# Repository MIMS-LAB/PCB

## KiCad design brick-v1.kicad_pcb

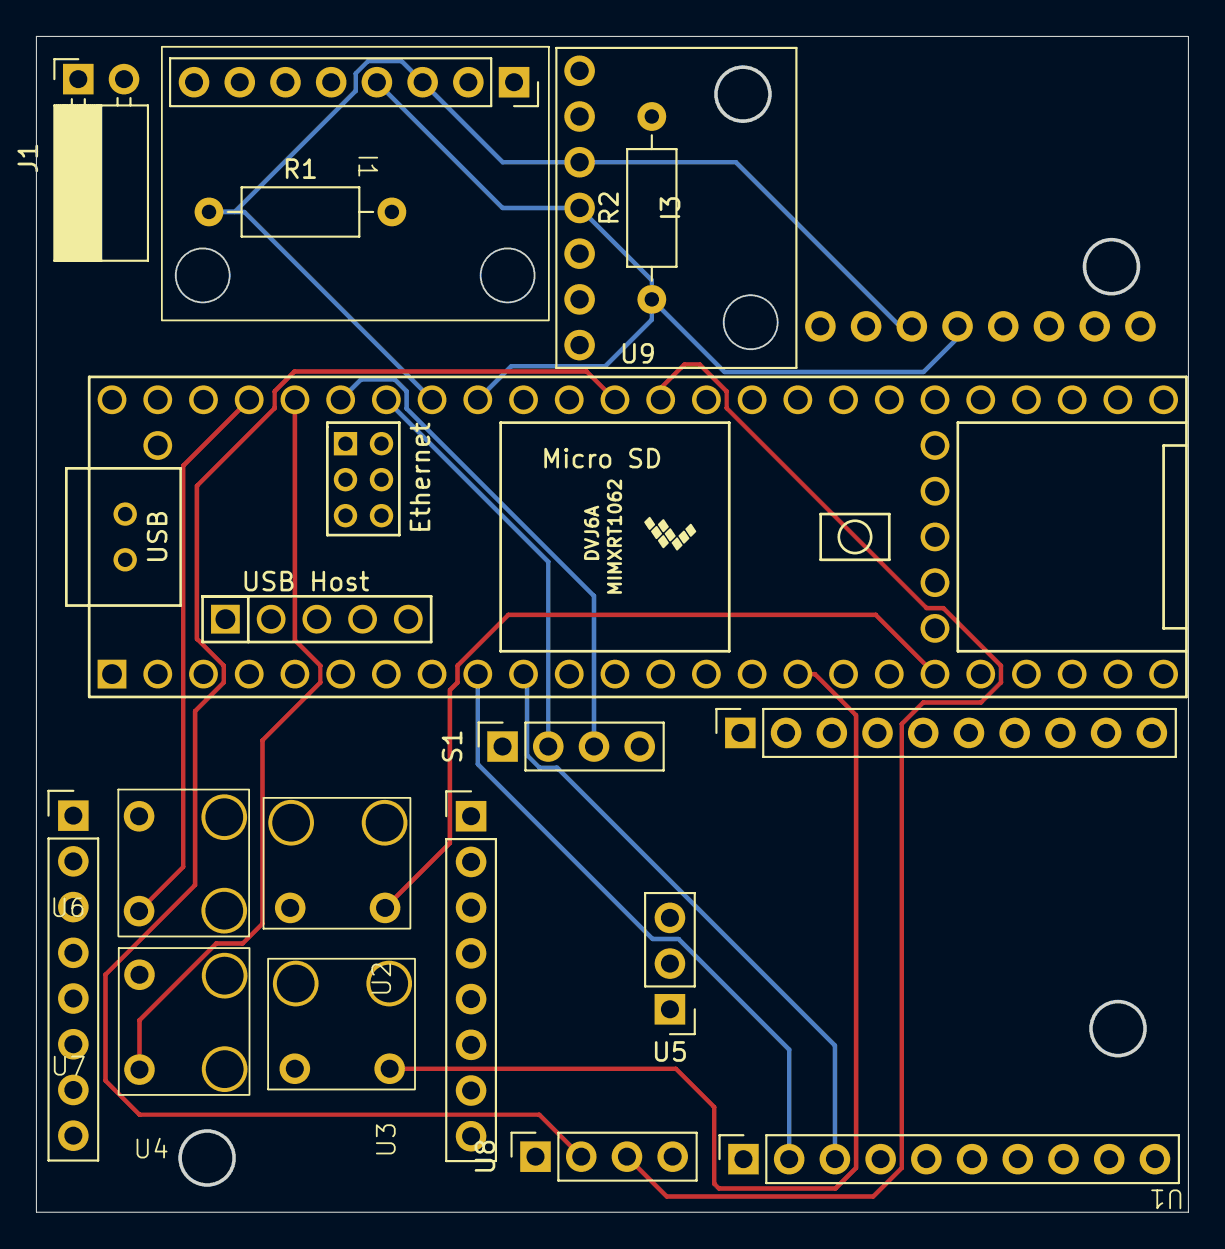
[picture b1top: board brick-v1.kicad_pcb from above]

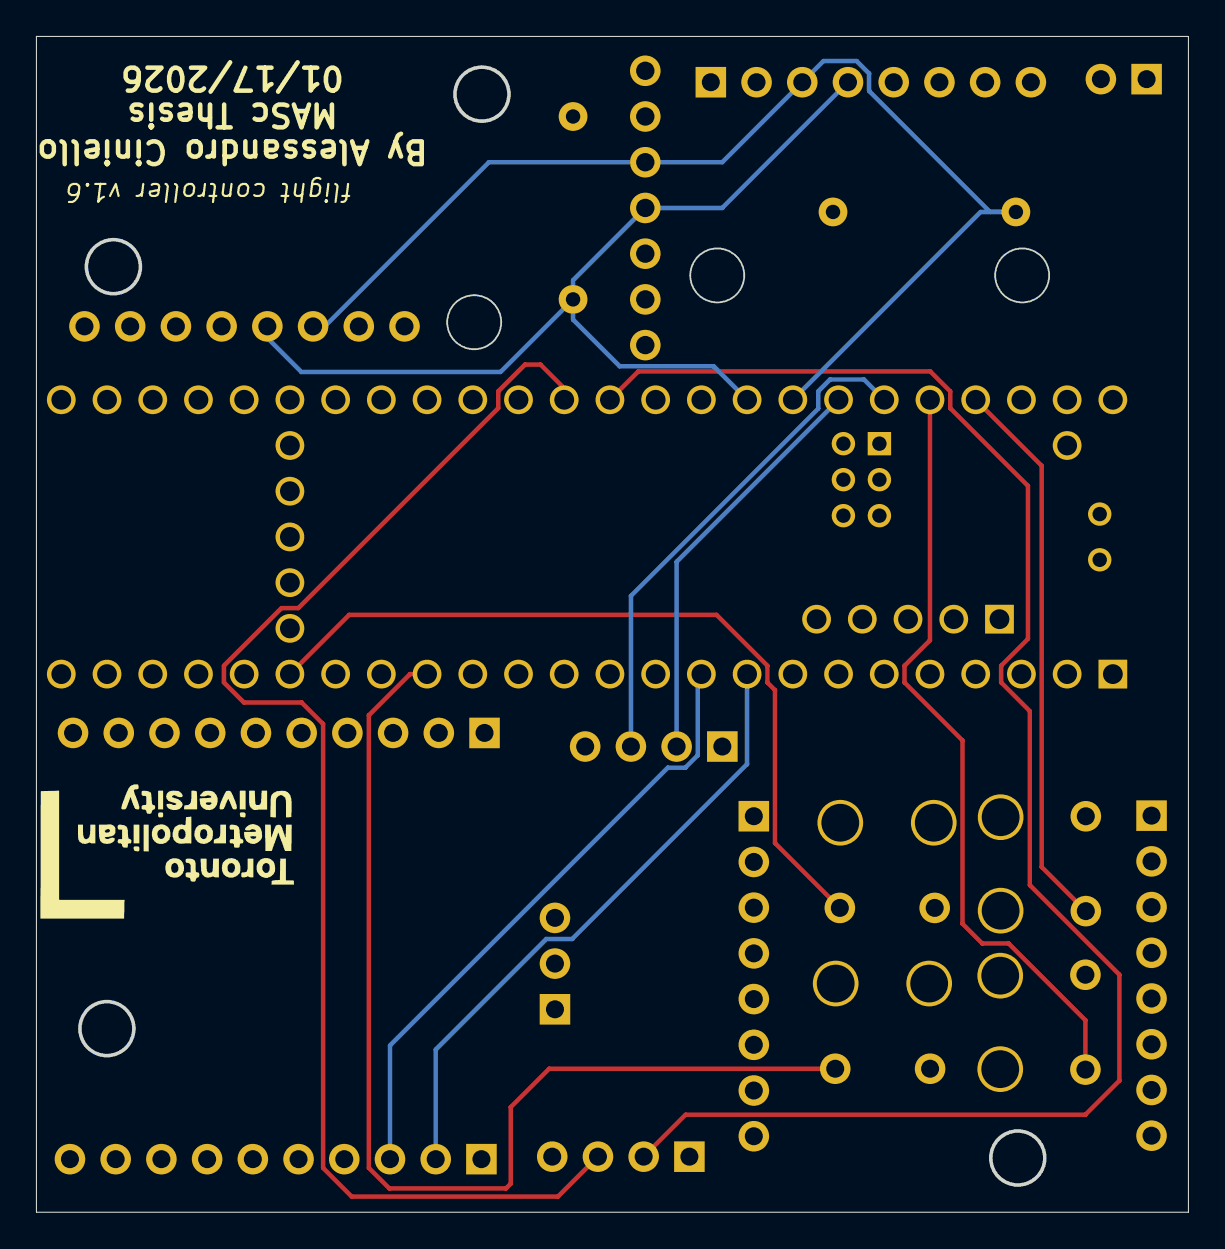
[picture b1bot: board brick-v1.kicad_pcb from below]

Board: 4 copper layers, 64.0 x 65.3 mm, 17 parts (2 on the bottom side), 16 nets.

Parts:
I1: MPU6050
I2: INA260
I3: MS5611; 1x07
J1: battery_header; PinSocket_1x02_P2.54mm_Horizontal
Logo1: picturae
R1, R2: R-Device; R_Axial_DIN0207_L6.3mm_D2.5mm_P10.16mm_Horizontal
S1: BN220-GPS; PinSocket_1x04_P2.54mm_Vertical
U1: XBEE S2C PRO; xbee_s2c
U2, U3, U6, U7: ESC; BLHeLi_esc
U4: esp32; esp32_cam
U5: L7805; PinHeader_1x03_P2.54mm_Vertical
U8: ULTRASONIC SENSOR; PinSocket_1x04_P2.54mm_Vertical
U9: Teensy4.1; Teensy41

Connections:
A0: U8.3 (ECHO), U9.14 (14_A0_TX3_SPDIF_OUT)
A1: U8.2 (TRIG), U9.15 (15_A1_RX3_SPDIF_IN)
A8: U7.4 (PWM), U9.22 (22_A8_CTX1)
A9: U6.4 (PWM), U9.23 (23_A9_CRX1_MCLK1)
A10: U3.4 (PWM), U9.24 (24_A10_TX6_SCL2)
A13: U2.4 (PWM), U9.27 (27_A13_SCK1)
GND: I1.2 (GND), I2.4 (GND), I3.2 (GND), J1.1, S1.4 (GND), U1.10 (GND), U2.2 (GND), U2.3 (T_GND), U3.2 (GND), U3.3 (T_GND), U4.2 (GND), U5.2 (GND), U6.2 (GND), U6.3 (T_GND), U7.2 (GND), U7.3 (T_GND), U8.4 (GND), U9.GND0 (GND), U9.GND2 (GND)
RX2: U1.2 (DOUT/DIO13), U9.7 (7_RX2_OUT1A)
RX5: S1.3 (TX), U9.21 (21_A7_RX5_BCLK1)
SCL: I1.3 (SCL), I2.5 (SCL), I3.3 (SCL), R1.1, U9.19 (19_A5_SCL)
SDA: I1.4 (SDA), I2.6 (SDA), I3.4 (SDA), R2.1, U9.18 (18_A4_SDA)
TX2: U1.3 (DIN/~CONFIG~{/DIO14), U9.8 (8_TX2_IN1)
TX5: S1.2 (RX), U9.20 (20_A6_TX5_LRCLK1)
T_VCC: I1.1 (VCC), I2.3 (VCC), I3.1 (VCC), R1.2, R2.2, U1.1 (VCC), U9.3.3V_1 (3V3)
VCC: S1.1 (VCC), U4.1 (VCC), U5.3 (OUT), U8.1 (VCC), U9.VIN
Vs: I2.1 (VIN+), J1.2, U2.1 (VCC), U3.1 (VCC), U5.1 (IN), U6.1 (VCC), U7.1 (VCC)

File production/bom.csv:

Designator,Footprint,Quantity,Value,LCSC Part #
I1,MPU6050,1,MPU6050,
I2,INA260,1,INA260,
I3,1x07,1,MS5611,
J1,PinSocket_1x02_P2.54mm_Horizontal,1,battery_header,
"LOGO1, LOGO2",picturae,2,~,
"R1, R2",R_Axial_DIN0207_L6.3mm_D2.5mm_P10.16mm_Horizontal,2,R-Device,
S1,PinSocket_1x04_P2.54mm_Vertical,1,BN220-GPS,
U1,xbee_s2c,1,XBEE S2C PRO,
"U2, U3, U6, U7",BLHeLi_esc,4,ESC,
U4,esp32_cam,1,esp32,
U5,PinHeader_1x03_P2.54mm_Vertical,1,L7805,
U8,PinSocket_1x04_P2.54mm_Vertical,1,ULTRASONIC SENSOR,
U9,Teensy41,1,Teensy4.1,

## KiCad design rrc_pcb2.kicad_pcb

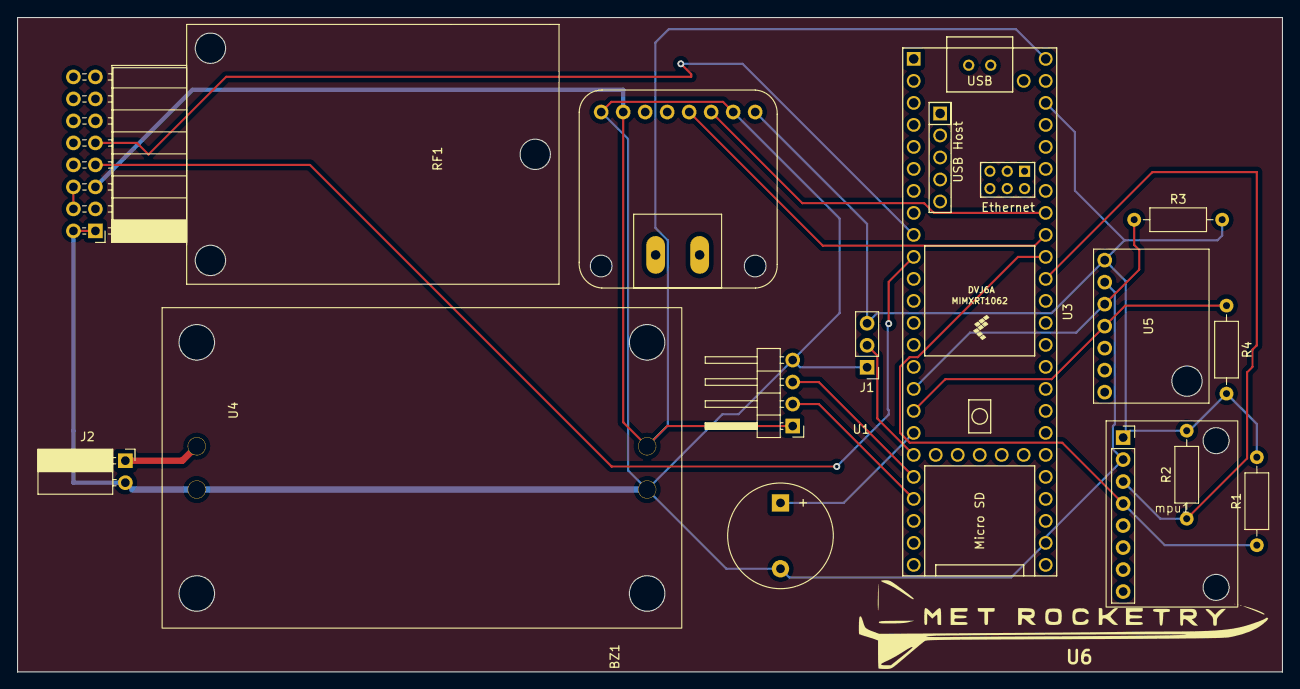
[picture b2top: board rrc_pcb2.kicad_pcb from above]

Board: 2 copper layers, 146.1 x 75.6 mm, 15 parts (0 on the bottom side), 15 nets.

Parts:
BZ1: Buzzer-Device; Buzzer_12x9.5RM7.6
J1: buzzer_toggle_pin; PinHeader_1x03_P2.54mm_Vertical
J2: battery_header; PinSocket_1x02_P2.54mm_Horizontal
R1, R2, R3, R4: R-Device; R_Axial_DIN0207_L6.3mm_D2.5mm_P10.16mm_Horizontal
RF1: RFD900+-RF_Module; RFD900+
U1: BN220-GPS; BN220
U2: INA260
U3: Teensy4.1; Teensy41
U4: voltReg
U5: MS5611; 1x07
U6: logo; RRC_logo
mpu1: MPU6050

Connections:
GND: BZ1.2 (+), J1.1, J2.2, RF1.GND, U1.4 (GND), U2.4 (GND), U2.10 (IN-), U3.34 (GND), U4.2 (GND), U4.4 (GND), U5.2 (GND), mpu1.2 (GND)
unnamed: BZ1.1 (-), U3.26 (26_A12_MOSI1)
unnamed: J1.2, U3.27 (27_A13_SCK1)
unnamed: J2.1, U4.1 (7.2V)
RX7: U1.3 (TX), U3.28 (28_RX7)
SCL: U2.5 (SCL), U3.19 (19_A5_SCL)
SCL1: R2.1, U3.16 (16_A2_RX4_SCL1), mpu1.3 (SCL)
SCL2: R3.1, U3.24 (24_A10_TX6_SCL2), U5.3 (SCL)
SDA: U2.6 (SDA), U3.18 (18_A4_SDA)
SDA1: R1.1, U3.17 (17_A3_TX4_SDA1), mpu1.4 (SDA)
SDA2: R4.1, U3.25 (25_A11_RX6_SDA2), U5.4 (SDA)
TX2: RF1.SIRX, U3.8 (8_TX2_IN1)
TX7: U1.2 (RX), U3.29 (29_TX7)
T_VCC: J1.3, R1.2, R2.2, R3.2, R4.2, U2.3 (VCC), U5.1 (VCC), mpu1.1 (VCC)
VCC: RF1.+5VUSB, U1.1 (VCC), U2.9 (IN+), U3.VIN, U4.3 (5V)

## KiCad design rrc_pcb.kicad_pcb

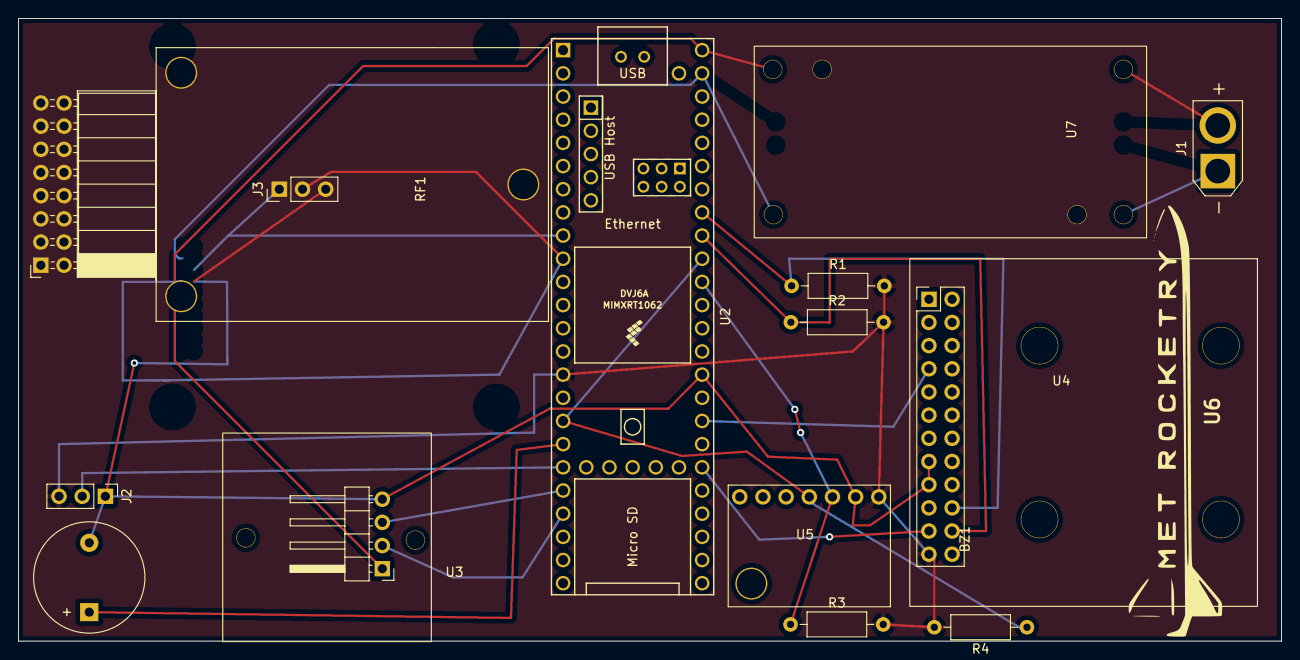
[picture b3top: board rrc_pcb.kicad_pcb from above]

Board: 2 copper layers, 138.4 x 68.2 mm, 15 parts (0 on the bottom side), 18 nets.

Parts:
BZ1: Buzzer-Device; Buzzer_12x9.5RM7.6
J1: Conn_01x02_Male-Connector; AMASS_XT30U-F_1x02_P5.0mm_Vertical
J2: Conn_01x03_Male-Connector; PinHeader_1x03_P2.54mm_Vertical
J3: digital logic connection; PinHeader_1x03_P2.54mm_Vertical
R1, R2, R3, R4: R-Device; R_Axial_DIN0207_L6.3mm_D2.5mm_P10.16mm_Horizontal
RF1: RFD900+-RF_Module; RFD900+
U2: Teensy4.1; Teensy41
U3: BN220-GPS; BN220
U4: ICM-20948; icm20948
U5: MS5611; 1x07
U6: logo; RRC_logo
U7: voltReg

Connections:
FSYNC: U2.30 (38_CS1_IN1), U4.21 (FSYNC)
GND: RF1.2 (GND), U2.47 (GND), U7.4 (GND)
INT1: U2.32 (40_A16), U4.7 (INT1)
unnamed: BZ1.1 (-), U2.18 (26_A12_MOSI1)
unnamed: J1.1, U7.1 (7.2V)
unnamed: J1.2, U7.2 (GND)
unnamed: J2.2, U2.19 (27_A13_SCK1)
RX2: J3.1, RF1.9 (SITX), U2.9 (7_RX2_OUT1A)
RX7: U2.20 (28_RX7), U3.3 (TX)
SCL: R1.1, U2.41 (19_A5_SCL), U4.20 (SCL/SCLK)
SCL1: R3.1, U2.38 (16_A2_RX4_SCL1), U5.3 (SCL)
SDA: R2.1, U2.40 (18_A4_SDA), U4.22 (SDA/SDI)
SDA1: R4.1, U2.17 (25_A11_RX6_SDA2), U2.39 (17_A3_TX4_SDA1), U5.4 (SDA)
TX2: J3.2, RF1.7 (SIRX), U2.10 (8_TX2_IN1)
TX7: U2.21 (29_TX7), U3.2 (RX)
T_GND: BZ1.2 (+), J2.1, J3.3, U2.34 (GND), U3.4 (GND), U4.15 (GND), U4.17 (GND), U5.2 (GND)
T_VCC: J2.3, R1.2, R2.2, R3.2, R4.2, U2.15 (3V3), U4.23 (Vin), U5.1 (VCC)
VCC: RF1.4 (+5V), U2.48 (VIN), U3.1 (VCC), U4.24 (AD0/SDO), U7.3 (5V)

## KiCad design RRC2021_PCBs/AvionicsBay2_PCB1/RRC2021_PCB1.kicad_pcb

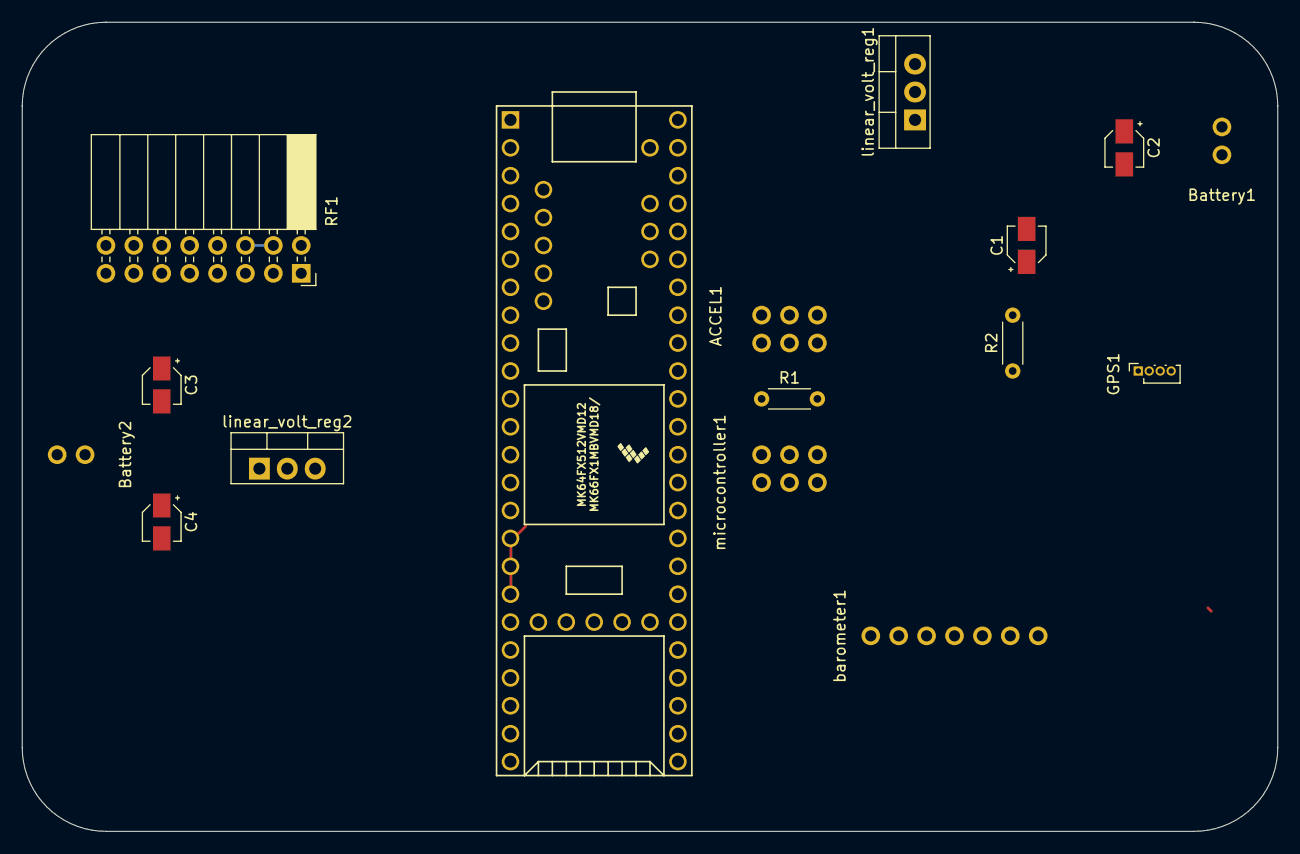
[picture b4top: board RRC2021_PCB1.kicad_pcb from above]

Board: 2 copper layers, 114.3 x 73.7 mm, 15 parts (0 on the bottom side), 15 nets.

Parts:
ACCEL1: ADXL357z; ADXLZ
Battery1, Battery2: 9V; 1x02
C1, C4: 0.33uF; CP_Elec_3x5.3
C2, C3: 0.1uF; CP_Elec_3x5.3
GPS1: BN220-GPS; PinSocket_1x04_P1.00mm_Vertical
R1, R2: 4.7KOHM-0603-1_10W-1%; R_Axial_DIN0204_L3.6mm_D1.6mm_P5.08mm_Horizontal
RF1: RFD900+; PinSocket_2x08_P2.54mm_Horizontal
barometer1: MS5611; 1x07
linear_volt_reg1, linear_volt_reg2: LM7805_TO220; TO-220-3_Vertical
microcontroller1: Teensy3.6; Teensy35_36

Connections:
unnamed: ACCEL1.1, R1.2, microcontroller1.46
unnamed: ACCEL1.2, GPS1.1, microcontroller1.39
unnamed: ACCEL1.3, R2.1, microcontroller1.45
unnamed: ACCEL1.5, ACCEL1.6, GPS1.4, R1.1, R2.2, microcontroller1.51
unnamed: Battery1.1, C1.1, linear_volt_reg1.1
unnamed: Battery1.2, C1.2, C2.2, linear_volt_reg1.2
unnamed: Battery2.1, C4.1, linear_volt_reg2.1
unnamed: Battery2.2, C3.2, C4.2, RF1.2, linear_volt_reg2.2
unnamed: C2.1, linear_volt_reg1.3, microcontroller1.53
unnamed: C3.1, RF1.5, linear_volt_reg2.3
unnamed: GPS1.2, microcontroller1.31
unnamed: GPS1.3, microcontroller1.30
unnamed: RF1.4, RF1.6
unnamed: RF1.7, microcontroller1.3
unnamed: RF1.9, microcontroller1.2

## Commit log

2021-07-14 added 2021 PCB
2021-07-18 updater and organize
2021-07-18 added rfd v5-vusb jumper
2021-07-18 add solder mask layer for plotting
2021-07-18 added mounting holes
2021-07-18 new pcb layout
2021-07-18 edit
2021-07-19 AC_added cool RRC logo
2021-07-20 added buzzer
2021-07-20 added buzzer enable pin
2021-07-21 moved standoffs around for better placement structurally , PCB is ready to go
2021-09-18 fixed prototype mistakes
    changed some drill holes positions
    changed GPS connector
    changed teensy used pins
2022-05-09 fixed pcb trace issues
2022-05-09 fixed pcb traces and moved stuff around
2022-05-09 edited gps mount
2022-05-12 fixed gps standoff points distances
2022-05-12 fixed rfd location
2022-05-13 fixed pcb and changed layout
2022-05-15 reoriented rfd
2022-05-15 buzzer fix
2022-05-15 finalized PCB
2022-05-18 fixed rfd900 clearance
2022-05-25 added gerber files:
2022-12-12 updated .sch
2022-12-16 update 2
    updated .sch added teensy4.1 , and updated footprints. Still in debugging stage
2022-12-17 updated pcb footprints
2022-12-17 optimized and finalized pcb
    reduced sizing and fixed traces.
2022-12-30 added edge cuts and mounting holes
2023-01-17 PCB is now ready to fabricate
    added gerbers and traces
2023-01-19 added pics
2023-02-24 tweaked srad main board
    tweaked iridium footprints and volt reg footprints and added a back board just in case iridium doenst pan out; uses rfd900p instead.
2023-04-15 fixed rfd traces
2023-04-30 rfd iteration f3
2023-05-31 Edit of PCB
2023-08-09 pcb update with new volt reg
2023-08-10 new pcb designs w/ new volt reg
2023-08-11 R1&R2 removed
2023-09-20 RFD footprint update
2023-12-06 UPDATED IMU and fixed some mounting holes
    replaced imu with mpu6050 and fixed batt header footprint and organized stuff
2023-12-06 fixed mpu footprint
2023-12-07 added 4 pin led
2024-02-01 edited led
2024-02-15 INA260
2024-02-22 updated pcb ina160 and traces
2024-03-07 PCB2
    Added INA to footprint, connected everything up, & generated gerber files.
2024-03-07 pcb gerber zip
2024-04-11 incr. thickness of traces
    0.25 to 1 mm
2024-07-19 updated rrc_pcb2 schematic and pcb files
2024-07-21 big cleanup of files
    also new teensy4.1 symbo(the accurate one now) and fixed rfd900 schematic
2024-07-21 fixed rfd and netlists for teensy4.1
    fixed the rfd netlists and teensy pwr netlists and also fixed the pinout and wiring for rfd
2024-07-22 small fixes to traces
    fixed pwr traces; moved them slightly away to avoid any possible bridging, also changed batt gnd to diff plate
2024-07-22 exported pcb to fabrication
    also fixed rfd rx trace
2025-04-15 organized
2025-04-16 v1.3 update
2025-04-16 updated traces
2025-04-17 editted footprints and symbol of xbee
2025-07-14 reorganized and fixed component error
    moved footprints around, replaced volt reg with smaller component and deleted thermistor
2025-07-14 fixed ina260 traces
2025-10-21 changed pcb size and sensor placements
2025-11-27 AC_flight controller updated v1.5
    -made 4 layer board
    -added esp32 camera
    -removed buzzer
    -reduced area of pcb
    -added TMU logos and my name and other descriptors
2026-01-06 deleted and organized footprints
